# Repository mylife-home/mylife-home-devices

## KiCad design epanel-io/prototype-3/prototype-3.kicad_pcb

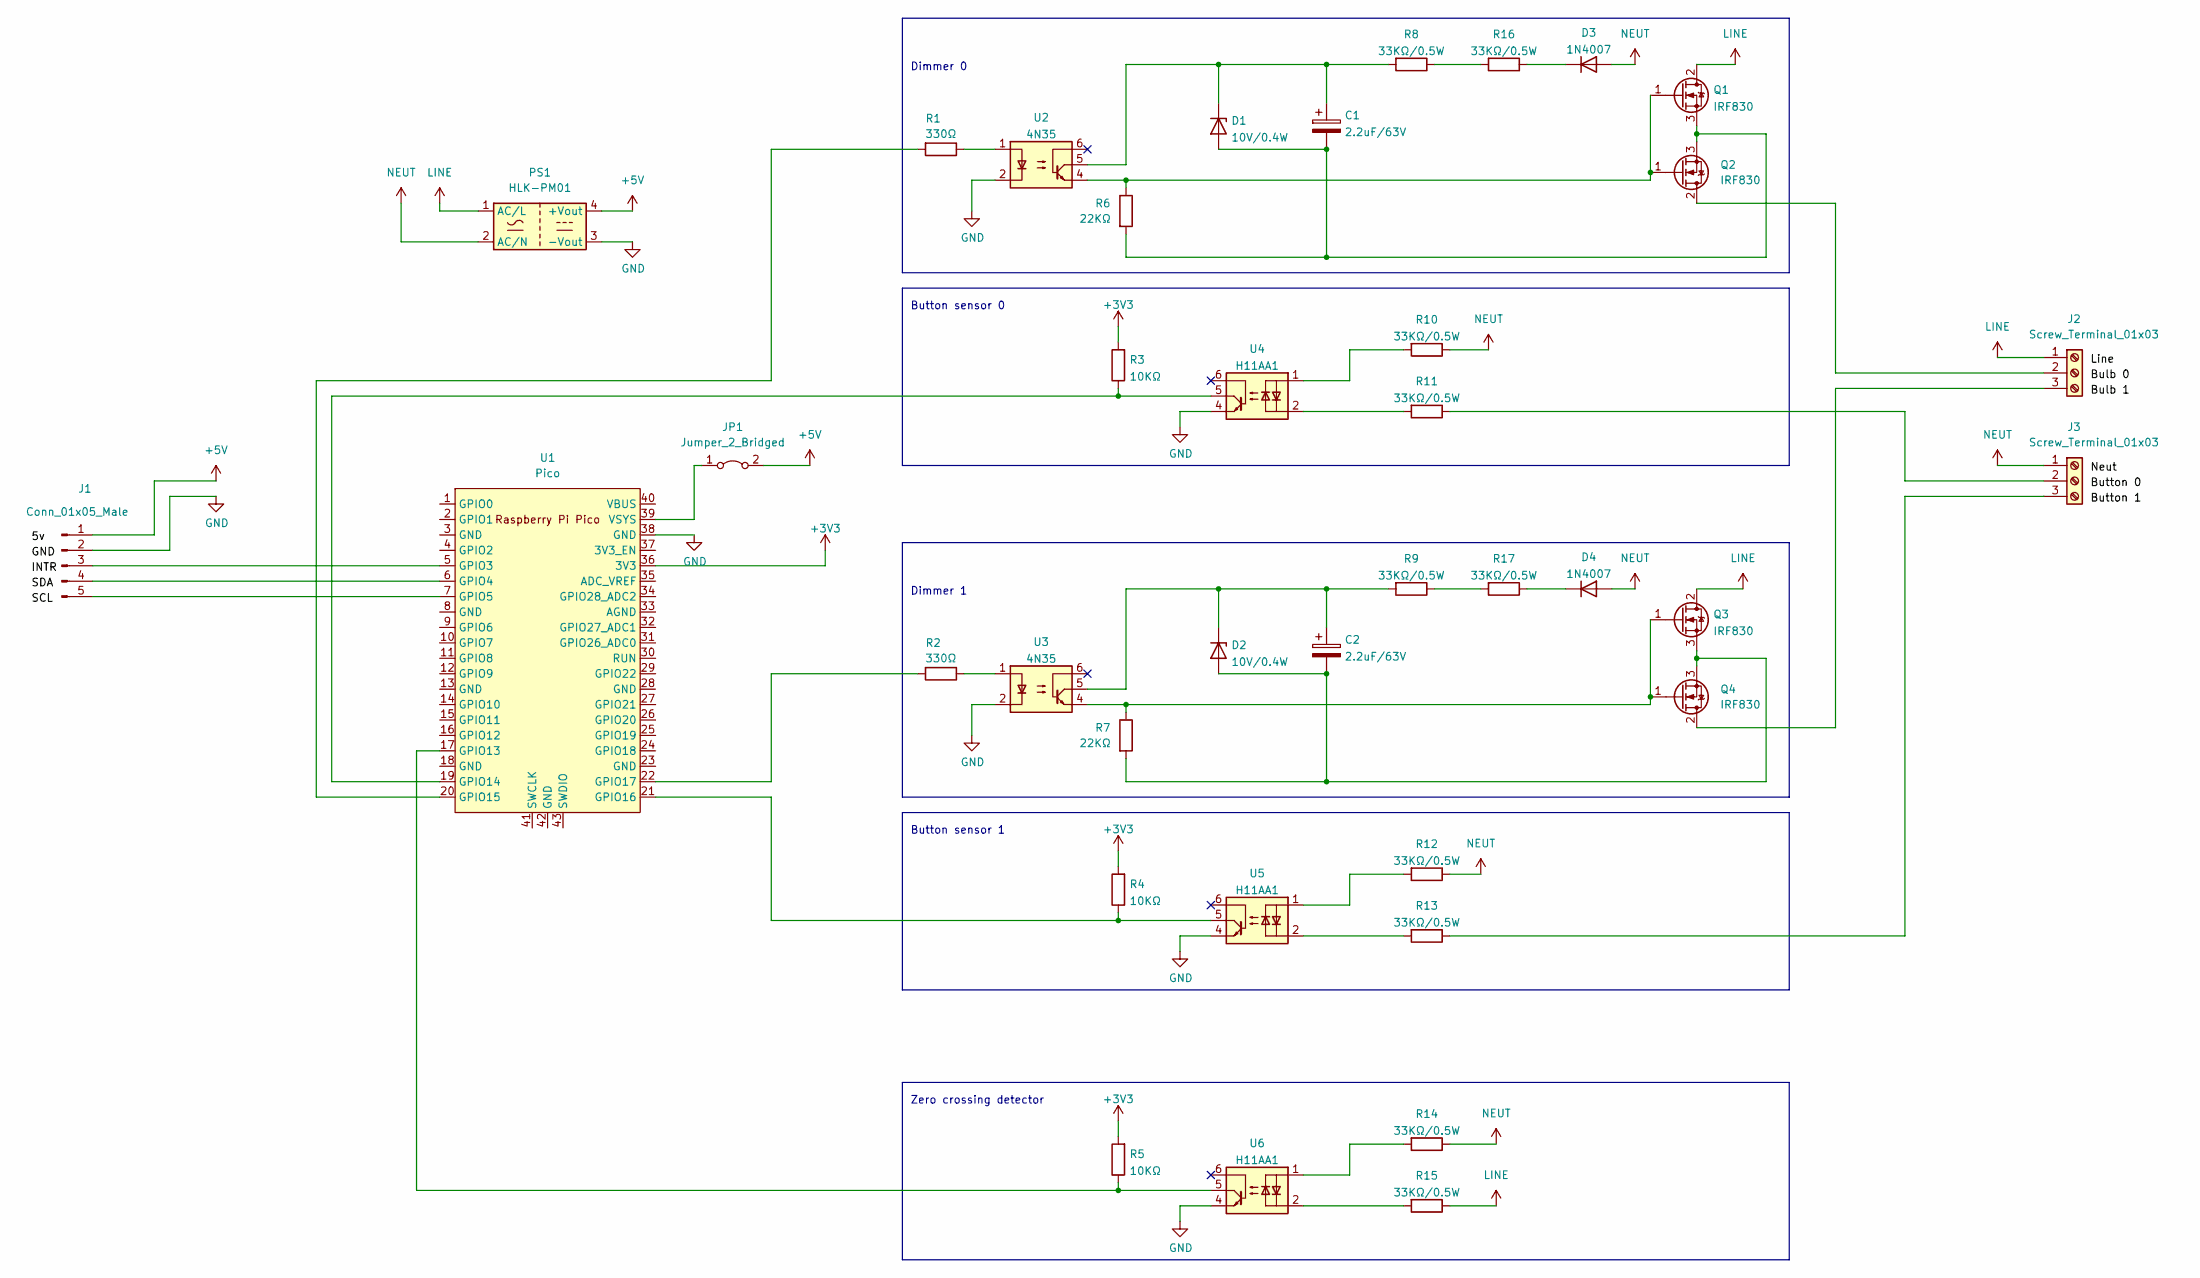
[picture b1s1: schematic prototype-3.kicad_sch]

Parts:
C1, C2: 2.2uF/63V; C_1206_3216Metric; LCSC C50254
D1, D2: 10V/0.4W; D_SOD-123; LCSC C173431
D3, D4: 1N4007; D_SMA; LCSC C727081
J1: Conn_01x05_Male; PinHeader_1x05_P2.54mm_Vertical
J2, J3: Screw_Terminal_01x03; TerminalBlock_bornier-3_P5.08mm
JP1: Jumper_2_Bridged; PinHeader_1x02_P2.54mm_Vertical
PS1: HLK-PM01; Converter_ACDC_HiLink_HLK-PMxx
Q1, Q2, Q3, Q4: IRF830; TO-263-3_TabPin2; LCSC C693297
R1, R2: 330Ω; R_0603_1608Metric; LCSC C23138
R3, R4, R5: 10KΩ; R_0603_1608Metric; LCSC C25804
R6, R7: 22KΩ; R_0603_1608Metric; LCSC C31850
R8, R9, R10, R11, R12, R13, R14, R15, R16, R17: 33KΩ/0.5W; R_0805_2012Metric; LCSC C966118
U1: Pico; RPi_Pico_SMD_TH
U2, U3: 4N35; SMDIP-6_W7.62mm; LCSC C115444
U4, U5, U6: H11AA1; SMDIP-6_W9.53mm; LCSC C184383

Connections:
+3V3: R3.2, R4.2, R5.2, U1.36 (3V3)
+5V: J1.1, JP1.2 (B), PS1.4 (+Vout)
GND: J1.2, PS1.3 (-Vout), U1.38 (GND), U2.2, U3.2, U4.4, U5.4, U6.4
LINE: J2.1, PS1.1 (AC/L), Q1.2 (D), Q3.2 (D), R15.1
NEUT: D3.2 (A), D4.2 (A), J3.1, PS1.2 (AC/N), R10.1, R12.1, R14.1
unnamed: C1.1, D1.1 (K), R8.2, U2.5
unnamed: C1.2, D1.2 (A), Q1.3 (S), Q2.3 (S), R6.2
unnamed: C2.1, D2.1 (K), R9.2, U3.5
unnamed: C2.2, D2.2 (A), Q3.3 (S), Q4.3 (S), R7.2
unnamed: D3.1 (K), R16.1
unnamed: D4.1 (K), R17.1
unnamed: J1.3, U1.5 (GPIO3)
unnamed: J1.4, U1.6 (GPIO4)
unnamed: J1.5, U1.7 (GPIO5)
unnamed: J2.2, Q2.2 (D)
unnamed: J2.3, Q4.2 (D)
unnamed: J3.2, R11.1
unnamed: J3.3, R13.1
unnamed: JP1.1 (A), U1.39 (VSYS)
unnamed: Q1.1 (G), Q2.1 (G), R6.1, U2.4
unnamed: Q3.1 (G), Q4.1 (G), R7.1, U3.4
unnamed: R1.1, U2.1
unnamed: R1.2, U1.20 (GPIO15)
unnamed: R2.1, U3.1
unnamed: R2.2, U1.22 (GPIO17)
unnamed: R3.1, U1.19 (GPIO14), U4.5
unnamed: R4.1, U1.21 (GPIO16), U5.5
unnamed: R5.1, U1.17 (GPIO13), U6.5
unnamed: R10.2, U4.1
unnamed: R11.2, U4.2
unnamed: R12.2, U5.1
unnamed: R13.2, U5.2
unnamed: R14.2, U6.1
unnamed: R15.2, U6.2
unnamed: R8.1, R16.2
unnamed: R9.1, R17.2

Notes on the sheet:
Button sensor 1
Button sensor 0
Dimmer 1
Dimmer 0
Zero crossing detector

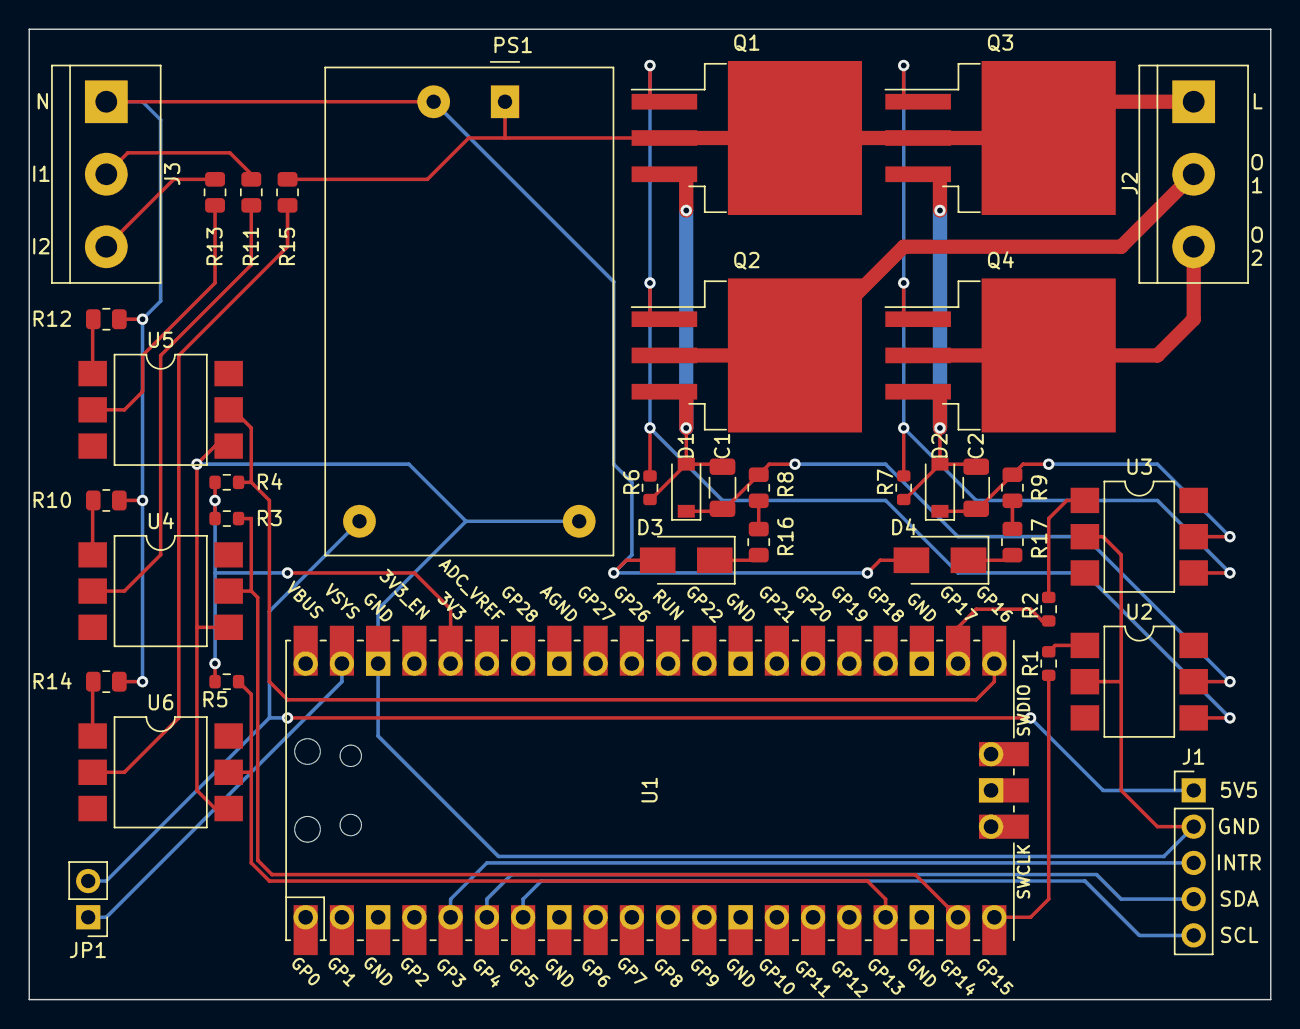
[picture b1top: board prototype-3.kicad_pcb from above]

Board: 2 copper layers, 87.0 x 68.0 mm, 38 parts (0 on the bottom side), 36 nets.

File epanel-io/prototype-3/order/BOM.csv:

Comment,Designator,Footprint,LCSC
"2.2uF/63V","C1,C2","Capacitor_SMD:C_1206_3216Metric","C50254"
"10V/0.4W","D1,D2","Diode_SMD:D_SOD-123","C173431"
"1N4007","D3,D4","Diode_SMD:D_SMA","C727081"
"Conn_01x05_Male","J1","Connector_PinHeader_2.54mm:PinHeader_1x05_P2.54mm_Vertical",""
"Screw_Terminal_01x03","J2,J3","TerminalBlock:TerminalBlock_bornier-3_P5.08mm",""
"Jumper_2_Bridged","JP1","Connector_PinHeader_2.54mm:PinHeader_1x02_P2.54mm_Vertical",""
"HLK-PM01","PS1","Converter_ACDC:Converter_ACDC_HiLink_HLK-PMxx",""
"IRF830","Q1,Q2,Q3,Q4","Package_TO_SOT_SMD:TO-263-3_TabPin2","C693297"
"330Ω","R1,R2","Resistor_SMD:R_0603_1608Metric","C23138"
"10KΩ","R3,R4,R5","Resistor_SMD:R_0603_1608Metric","C25804"
"22KΩ","R6,R7","Resistor_SMD:R_0603_1608Metric","C31850"
"33KΩ/0.5W","R8,R9,R10,R11,R12,R13,R14,R15,R16,R17","Resistor_SMD:R_0805_2012Metric","C966118"
"Pico","U1","MCU_RaspberryPi_and_Boards:RPi_Pico_SMD_TH",""
"4N35","U2,U3","Package_DIP:SMDIP-6_W7.62mm","C115444"
"H11AA1","U4,U5,U6","Package_DIP:SMDIP-6_W9.53mm","C184383"

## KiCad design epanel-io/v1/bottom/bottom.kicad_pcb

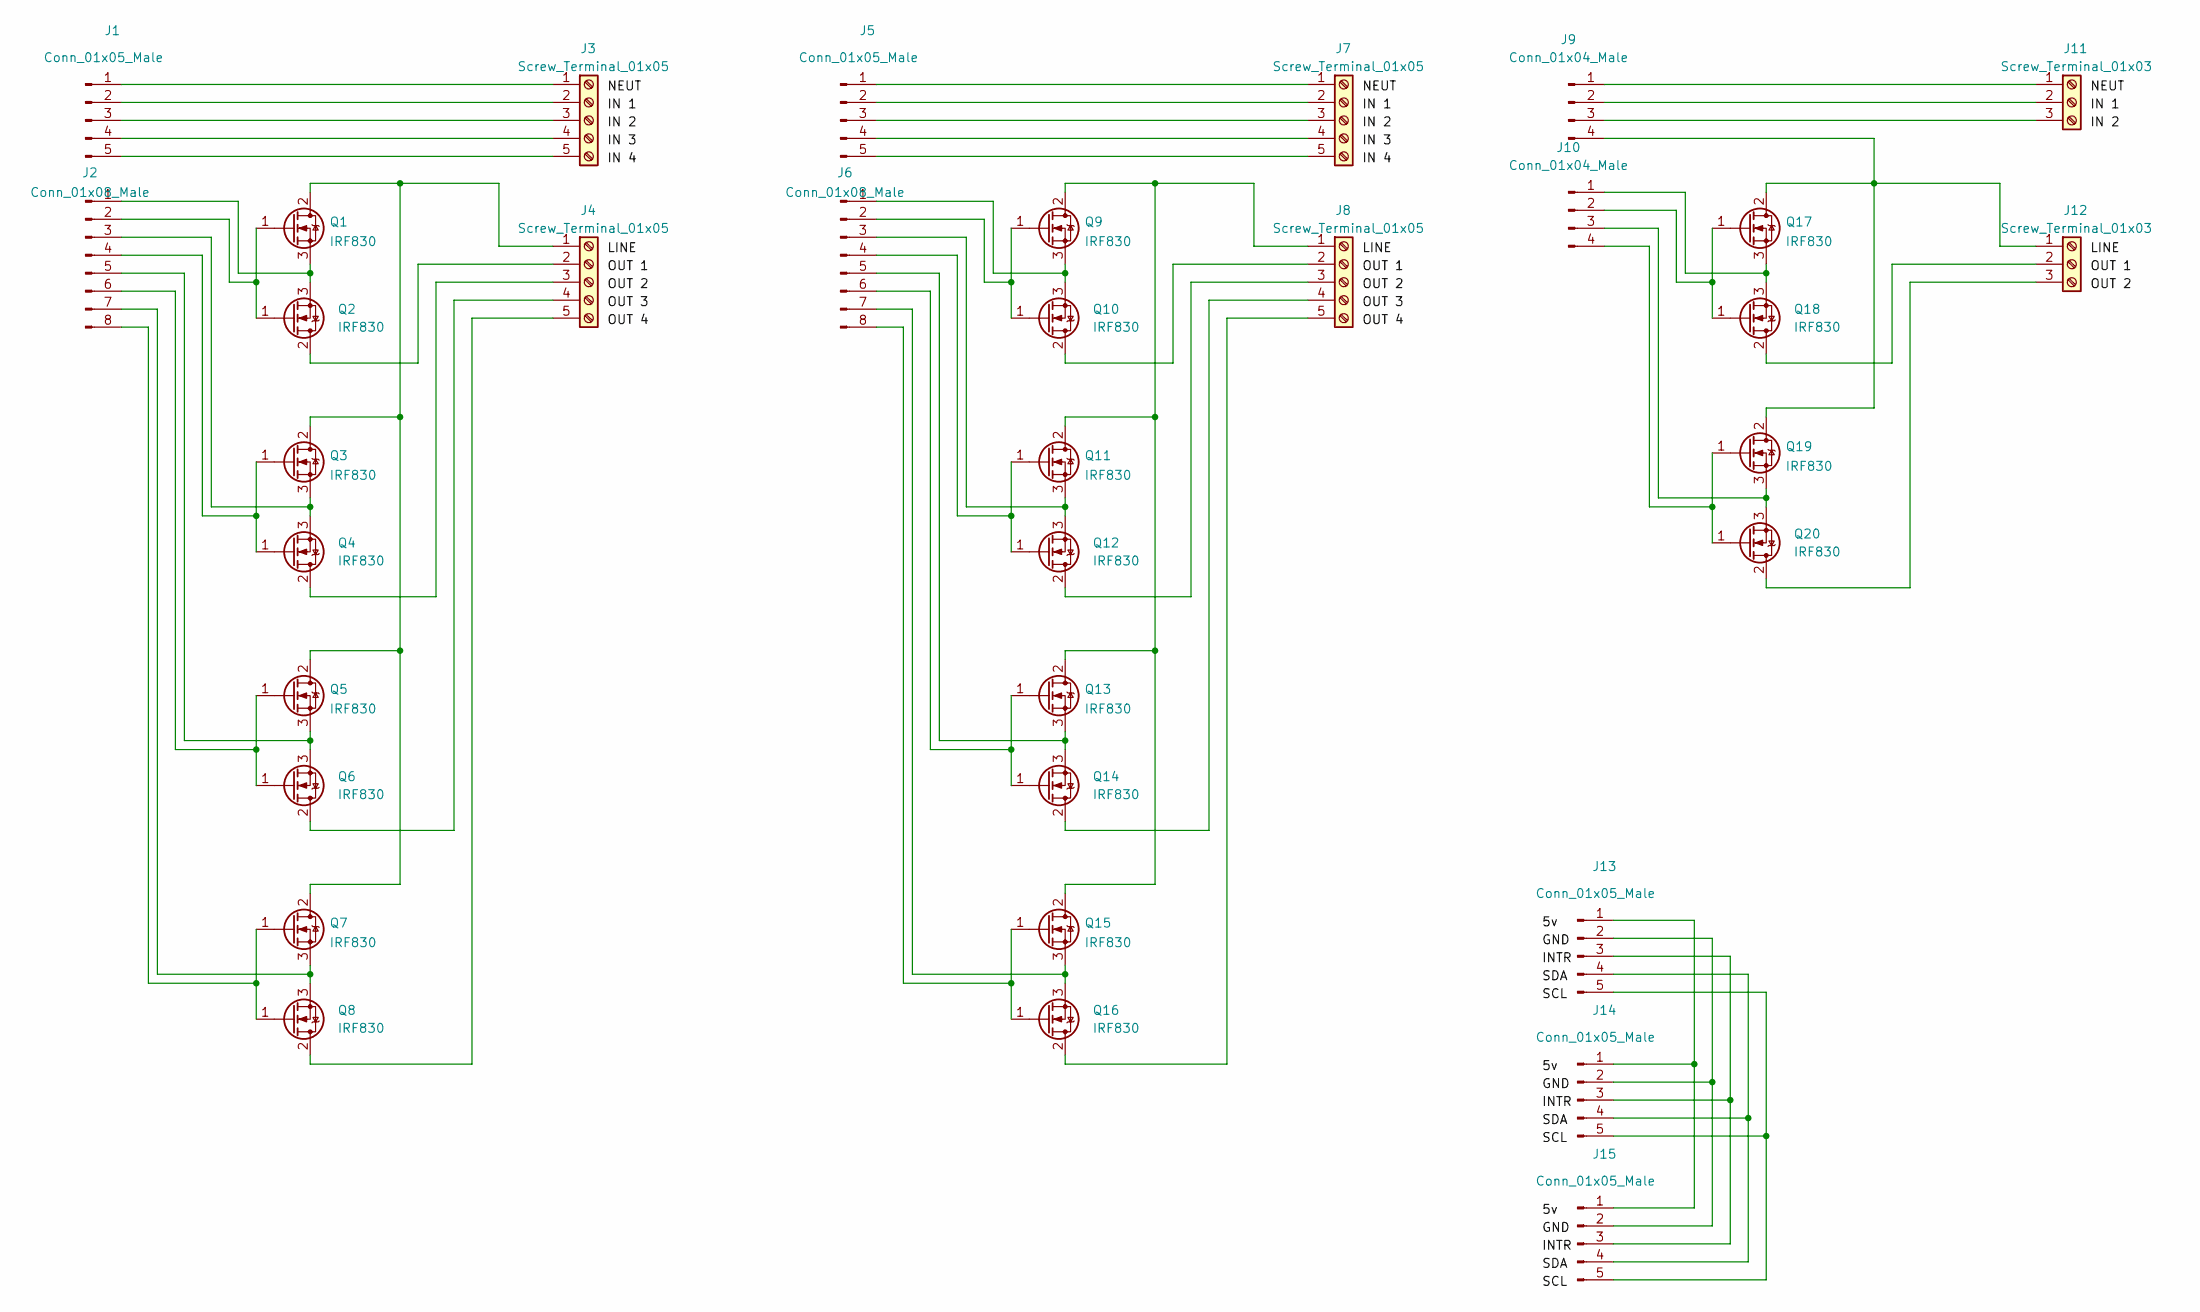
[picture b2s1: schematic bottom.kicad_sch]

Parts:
J1, J5, J13, J14, J15: Conn_01x05_Male; PinHeader_1x05_P2.54mm_Vertical
J2, J6: Conn_01x08_Male; PinHeader_1x08_P2.54mm_Vertical
J3, J4, J7, J8: Screw_Terminal_01x05; TerminalBlock_bornier-5_P5.08mm
J9, J10: Conn_01x04_Male; PinHeader_1x04_P2.54mm_Vertical
J11, J12: Screw_Terminal_01x03; TerminalBlock_bornier-3_P5.08mm
Q1, Q2, Q3, Q4, Q5, Q6, Q7, Q8, Q9, Q10, Q11, Q12, Q13, Q14, Q15, Q16, Q17, Q18, Q19, Q20: IRF830; TO-263-3_TabPin2; LCSC C693297

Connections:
unnamed: J1.1, J3.1
unnamed: J1.2, J3.2
unnamed: J1.3, J3.3
unnamed: J1.4, J3.4
unnamed: J1.5, J3.5
unnamed: J2.1, Q1.3 (S), Q2.3 (S)
unnamed: J2.2, Q1.1 (G), Q2.1 (G)
unnamed: J2.3, Q3.3 (S), Q4.3 (S)
unnamed: J2.4, Q3.1 (G), Q4.1 (G)
unnamed: J2.5, Q5.3 (S), Q6.3 (S)
unnamed: J2.6, Q5.1 (G), Q6.1 (G)
unnamed: J2.7, Q7.3 (S), Q8.3 (S)
unnamed: J2.8, Q7.1 (G), Q8.1 (G)
unnamed: J4.1, Q1.2 (D), Q3.2 (D), Q5.2 (D), Q7.2 (D)
unnamed: J4.2, Q2.2 (D)
unnamed: J4.3, Q4.2 (D)
unnamed: J4.4, Q6.2 (D)
unnamed: J4.5, Q8.2 (D)
unnamed: J5.1, J7.1
unnamed: J5.2, J7.2
unnamed: J5.3, J7.3
unnamed: J5.4, J7.4
unnamed: J5.5, J7.5
unnamed: J6.1, Q9.3 (S), Q10.3 (S)
unnamed: J6.2, Q9.1 (G), Q10.1 (G)
unnamed: J6.3, Q11.3 (S), Q12.3 (S)
unnamed: J6.4, Q11.1 (G), Q12.1 (G)
unnamed: J6.5, Q13.3 (S), Q14.3 (S)
unnamed: J6.6, Q13.1 (G), Q14.1 (G)
unnamed: J6.7, Q15.3 (S), Q16.3 (S)
unnamed: J6.8, Q15.1 (G), Q16.1 (G)
unnamed: J8.1, Q9.2 (D), Q11.2 (D), Q13.2 (D), Q15.2 (D)
unnamed: J8.2, Q10.2 (D)
unnamed: J8.3, Q12.2 (D)
unnamed: J8.4, Q14.2 (D)
unnamed: J8.5, Q16.2 (D)
unnamed: J10.1, Q17.3 (S), Q18.3 (S)
unnamed: J10.2, Q17.1 (G), Q18.1 (G)
unnamed: J10.3, Q19.3 (S), Q20.3 (S)
unnamed: J10.4, Q19.1 (G), Q20.1 (G)
unnamed: J9.1, J11.1
unnamed: J9.2, J11.2
unnamed: J9.3, J11.3
unnamed: J9.4, J12.1, Q17.2 (D), Q19.2 (D)
unnamed: J12.2, Q18.2 (D)
unnamed: J12.3, Q20.2 (D)
unnamed: J13.1, J14.1, J15.1
unnamed: J13.2, J14.2, J15.2
unnamed: J13.3, J14.3, J15.3
unnamed: J13.4, J14.4, J15.4
unnamed: J13.5, J14.5, J15.5

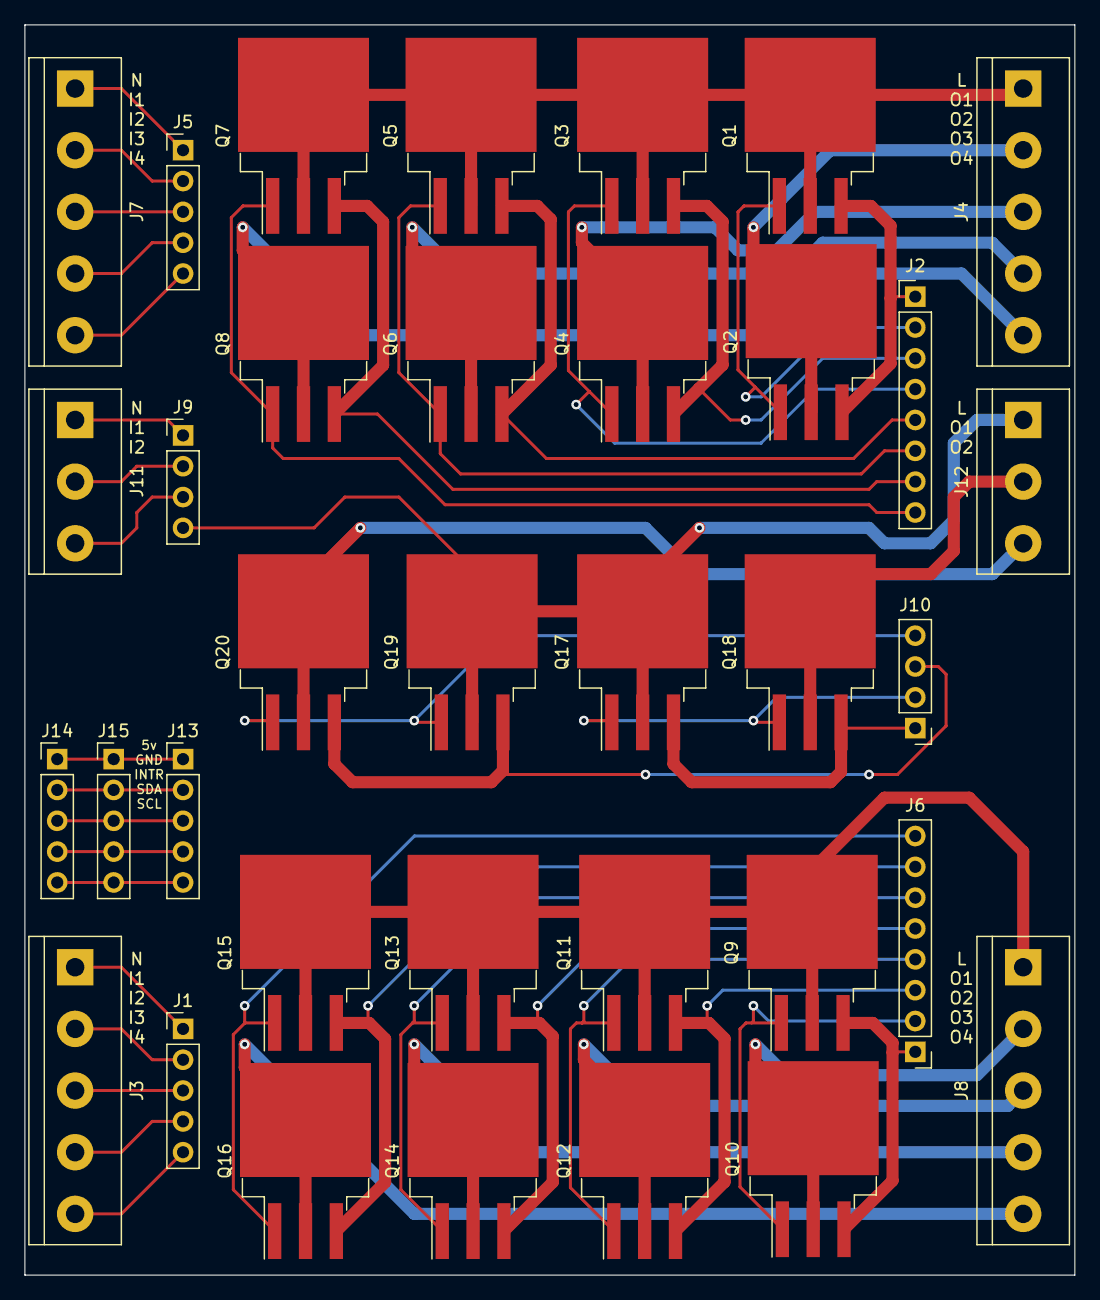
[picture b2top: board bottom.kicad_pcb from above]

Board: 2 copper layers, 86.5 x 103.0 mm, 35 parts (0 on the bottom side), 51 nets.

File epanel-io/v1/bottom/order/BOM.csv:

Comment,Designator,Footprint,LCSC
"Conn_01x05_Male","J1,J5,J13,J14,J15","Connector_PinHeader_2.54mm:PinHeader_1x05_P2.54mm_Vertical",""
"Screw_Terminal_01x03","J11,J12","TerminalBlock:TerminalBlock_bornier-3_P5.08mm",""
"Conn_01x08_Male","J2,J6","Connector_PinHeader_2.54mm:PinHeader_1x08_P2.54mm_Vertical",""
"Screw_Terminal_01x05","J3,J4,J7,J8","TerminalBlock:TerminalBlock_bornier-5_P5.08mm",""
"Conn_01x04_Male","J9,J10","Connector_PinHeader_2.54mm:PinHeader_1x04_P2.54mm_Vertical",""
"IRF830","Q1,Q2,Q3,Q4,Q5,Q6,Q7,Q8,Q9,Q10,Q11,Q12,Q13,Q14,Q15,Q16,Q17,Q18,Q19,Q20","Package_TO_SOT_SMD:TO-263-3_TabPin2","C693297"

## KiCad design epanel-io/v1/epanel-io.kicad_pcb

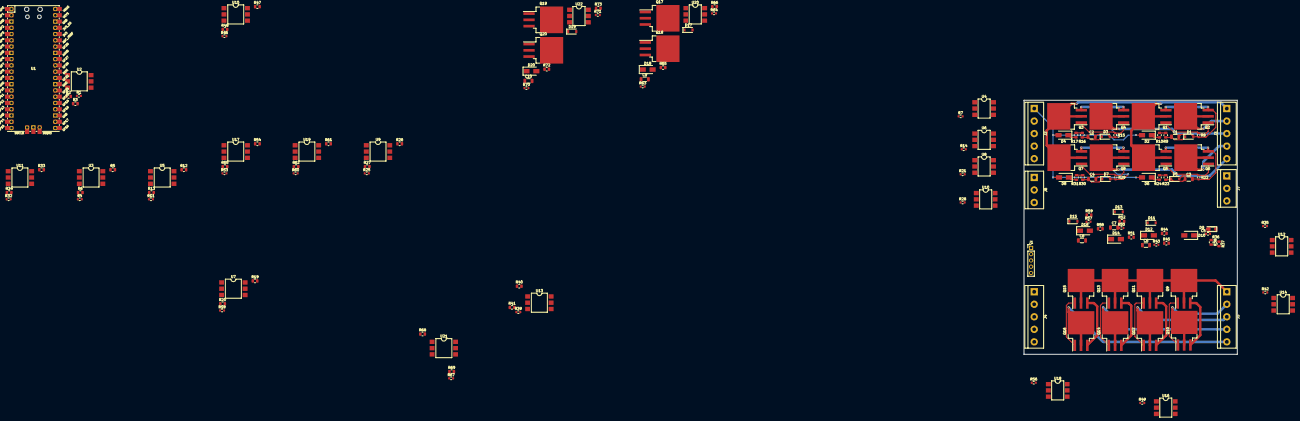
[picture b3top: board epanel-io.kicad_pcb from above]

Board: 2 copper layers, 86.5 x 103.0 mm, 152 parts (0 on the bottom side), 135 nets.

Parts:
C1, C2, C3, C4, C5, C6, C7, C8, C9, C10: 2.2uF/63V; C_1206_3216Metric
D1, D3, D5, D7, D9, D11, D13, D15, D17, D19: 10V/0.4W; D_SOD-123
D2, D4, D6, D8, D10, D12, D14, D16, D18, D20: 1N4007; D_SMA
J1: Conn_01x05_Male; PinHeader_1x05_P2.54mm_Vertical
J2, J3, J4, J5: Screw_Terminal_01x05; TerminalBlock_bornier-5_P5.08mm
J6, J7: Screw_Terminal_01x03; TerminalBlock_bornier-3_P5.08mm
Q1, Q2, Q3, Q4, Q5, Q6, Q7, Q8, Q9, Q10, Q11, Q12, Q13, Q14, Q15, Q16, Q17, Q18, Q19, Q20: IRF830; TO-263-3_TabPin2
R1, R4, R11, R18, R25, R32, R39, R46, R53, R60, R67: 10KΩ; R_0603_1608Metric
R2, R3, R5, R6, R9, R10, R12, R13, R16, R17, R19, R20, R23, R24, R26, R27, R30, R31, R33, R34, R37, R38, R40, R41, R44, R45, R47, R48, R51, R52, R54, R55, R58, R59, R61, R62, R65, R66, R68, R69, R72, R73: 33KΩ/0.5W; R_0805_2012Metric
R7, R14, R21, R28, R35, R42, R49, R56, R63, R70: 330Ω; R_0603_1608Metric
R8, R15, R22, R29, R36, R43, R50, R57, R64, R71: 22KΩ; R_0603_1608Metric
U1: Pico; RPi_Pico_SMD_TH
U2, U3, U5, U7, U9, U11, U13, U15, U17, U19, U21: H11AA1; SMDIP-6_W9.53mm
U4, U6, U8, U10, U12, U14, U16, U18, U20, U22: 4N35; SMDIP-6_W7.62mm

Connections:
+3V3: R1.2, R4.2, R11.2, R18.2, R25.2, R32.2, R39.2, R46.2, R53.2, R60.2, R67.2, U1.36 (3V3)
+5V: J1.1, U1.39 (VSYS)
/Input 1/INPUT: J2.2, R6.1
/Input 1/NEUT: D2.2 (A), D4.2 (A), D6.2 (A), D8.2 (A), J2.1, R5.1, R12.1, R19.1, R26.1
/Input 1/RPI: R4.1, U1.9 (GPIO6), U3.5
/Input 2/INPUT: J2.3, R13.1
/Input 2/RPI: R11.1, U1.10 (GPIO7), U5.5
/Input 3/INPUT: J2.4, R20.1
/Input 3/RPI: R18.1, U1.11 (GPIO8), U7.5
/Input 4/INPUT: J2.5, R27.1
/Input 4/RPI: R25.1, U1.12 (GPIO9), U9.5
/Input 5/INPUT: J4.2, R34.1
/Input 5/NEUT: D10.2 (A), D12.2 (A), D14.2 (A), D16.2 (A), J4.1, R33.1, R40.1, R47.1, R54.1
/Input 5/RPI: R32.1, U1.19 (GPIO14), U11.5
/Input 6/INPUT: J4.3, R41.1
/Input 6/RPI: R39.1, U1.20 (GPIO15), U13.5
/Input 7/INPUT: J4.4, R48.1
/Input 7/RPI: R46.1, U1.21 (GPIO16), U15.5
/Input 8/INPUT: J4.5, R55.1
/Input 8/RPI: R53.1, U1.22 (GPIO17), U17.5
/Input 9/INPUT: J6.2, R62.1
/Input 9/RPI: R60.1, U1.29 (GPIO22), U19.5
/Input 10/INPUT: J6.3, R69.1
/Input 10/NEUT: D18.2 (A), D20.2 (A), J6.1, R2.1, R61.1, R68.1
/Input 10/RPI: R67.1, U1.31 (GPIO26_ADC0), U21.5
/Output 1/LINE: J3.1, Q1.2 (D), Q3.2 (D), Q5.2 (D), Q7.2 (D)
/Output 1/OUTPUT: J3.2, Q2.2 (D)
/Output 1/RPI: R7.2, U1.14 (GPIO10)
/Output 2/OUTPUT: J3.3, Q4.2 (D)
/Output 2/RPI: R14.2, U1.15 (GPIO11)
/Output 3/OUTPUT: J3.4, Q6.2 (D)
/Output 3/RPI: R21.2, U1.16 (GPIO12)
/Output 4/OUTPUT: J3.5, Q8.2 (D)
/Output 4/RPI: R28.2, U1.17 (GPIO13)
/Output 5/LINE: J5.1, Q9.2 (D), Q11.2 (D), Q13.2 (D), Q15.2 (D)
/Output 5/OUTPUT: J5.2, Q10.2 (D)
/Output 5/RPI: R35.2, U1.24 (GPIO18)
/Output 6/OUTPUT: J5.4, Q14.2 (D)
/Output 6/RPI: R49.2, U1.26 (GPIO20)
/Output 7/OUTPUT: J5.3, Q12.2 (D)
/Output 7/RPI: R42.2, U1.25 (GPIO19)
/Output 8/OUTPUT: J5.5, Q16.2 (D)
/Output 8/RPI: R56.2, U1.27 (GPIO21)
/Output 9/OUTPUT: J7.2, Q18.2 (D)
/Output 9/RPI: R63.2, U1.32 (GPIO27_ADC1)
/Output 10/LINE: J7.1, Q17.2 (D), Q19.2 (D), R3.1
/Output 10/OUTPUT: J7.3, Q20.2 (D)
/Output 10/RPI: R70.2, U1.34 (GPIO28_ADC2)
GND: J1.2, U1.38 (GND), U2.4, U3.4, U4.2, U5.4, U6.2, U7.4, U8.2, U9.4, U10.2, U11.4, U12.2, U13.4, U14.2, U15.4, U16.2, U17.4, U18.2, U19.4, U20.2, U21.4, U22.2
unnamed: C1.1, D1.1 (K), R9.2, U4.5
unnamed: C1.2, D1.2 (A), Q1.3 (S), Q2.3 (S), R8.2
unnamed: C2.1, D3.1 (K), R16.2, U6.5
unnamed: C2.2, D3.2 (A), Q3.3 (S), Q4.3 (S), R15.2
unnamed: C3.1, D5.1 (K), R23.2, U8.5
unnamed: C3.2, D5.2 (A), Q5.3 (S), Q6.3 (S), R22.2
unnamed: C4.1, D7.1 (K), R30.2, U10.5
unnamed: C4.2, D7.2 (A), Q7.3 (S), Q8.3 (S), R29.2
unnamed: C5.1, D9.1 (K), R37.2, U12.5
unnamed: C5.2, D9.2 (A), Q9.3 (S), Q10.3 (S), R36.2
unnamed: C6.1, D11.1 (K), R44.2, U14.5
unnamed: C6.2, D11.2 (A), Q11.3 (S), Q12.3 (S), R43.2
unnamed: C7.1, D13.1 (K), R51.2, U16.5
unnamed: C7.2, D13.2 (A), Q13.3 (S), Q14.3 (S), R50.2
unnamed: C8.1, D15.1 (K), R58.2, U18.5
unnamed: C8.2, D15.2 (A), Q15.3 (S), Q16.3 (S), R57.2
unnamed: C9.1, D17.1 (K), R65.2, U20.5
unnamed: C9.2, D17.2 (A), Q17.3 (S), Q18.3 (S), R64.2
unnamed: C10.1, D19.1 (K), R72.2, U22.5
unnamed: C10.2, D19.2 (A), Q19.3 (S), Q20.3 (S), R71.2
unnamed: D2.1 (K), R10.1
unnamed: D4.1 (K), R17.1
unnamed: D6.1 (K), R24.1
unnamed: D8.1 (K), R31.1
unnamed: D10.1 (K), R38.1
unnamed: D12.1 (K), R45.1
unnamed: D14.1 (K), R52.1
unnamed: D16.1 (K), R59.1
unnamed: D18.1 (K), R66.1
unnamed: D20.1 (K), R73.1
unnamed: J1.3, U1.5 (GPIO3)
unnamed: J1.4, U1.6 (GPIO4)
unnamed: J1.5, U1.7 (GPIO5)
unnamed: Q1.1 (G), Q2.1 (G), R8.1, U4.4
unnamed: Q3.1 (G), Q4.1 (G), R15.1, U6.4
unnamed: Q5.1 (G), Q6.1 (G), R22.1, U8.4
unnamed: Q7.1 (G), Q8.1 (G), R29.1, U10.4
unnamed: Q9.1 (G), Q10.1 (G), R36.1, U12.4
unnamed: Q11.1 (G), Q12.1 (G), R43.1, U14.4
unnamed: Q13.1 (G), Q14.1 (G), R50.1, U16.4
unnamed: Q15.1 (G), Q16.1 (G), R57.1, U18.4
unnamed: Q17.1 (G), Q18.1 (G), R64.1, U20.4
unnamed: Q19.1 (G), Q20.1 (G), R71.1, U22.4
unnamed: R1.1, U1.4 (GPIO2), U2.5
unnamed: R2.2, U2.1
unnamed: R3.2, U2.2
unnamed: R5.2, U3.1
unnamed: R6.2, U3.2
unnamed: R7.1, U4.1
unnamed: R9.1, R10.2
unnamed: R12.2, U5.1
unnamed: R13.2, U5.2
unnamed: R14.1, U6.1
unnamed: R16.1, R17.2
unnamed: R19.2, U7.1
unnamed: R20.2, U7.2
unnamed: R21.1, U8.1
unnamed: R23.1, R24.2
unnamed: R26.2, U9.1
unnamed: R27.2, U9.2
unnamed: R28.1, U10.1
unnamed: R30.1, R31.2
unnamed: R33.2, U11.1
unnamed: R34.2, U11.2
unnamed: R35.1, U12.1
unnamed: R37.1, R38.2
unnamed: R40.2, U13.1
unnamed: R41.2, U13.2
unnamed: R42.1, U14.1
unnamed: R44.1, R45.2
unnamed: R47.2, U15.1
unnamed: R48.2, U15.2
unnamed: R49.1, U16.1
unnamed: R51.1, R52.2
unnamed: R54.2, U17.1
unnamed: R55.2, U17.2
unnamed: R56.1, U18.1
unnamed: R58.1, R59.2
unnamed: R61.2, U19.1
unnamed: R62.2, U19.2
unnamed: R63.1, U20.1
unnamed: R65.1, R66.2
unnamed: R68.2, U21.1
unnamed: R69.2, U21.2
unnamed: R70.1, U22.1
unnamed: R72.1, R73.2

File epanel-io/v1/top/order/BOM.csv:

Comment,Designator,Footprint,LCSC
"2.2uF/63V","C1,C2,C3,C4,C5,C6,C7,C8,C9,C10","Capacitor_SMD:C_1206_3216Metric","C50254"
"10V/0.4W","D1,D3,D5,D7,D9,D11,D13,D15,D17,D19","Diode_SMD:D_SOD-123","C173431"
"1N4007","D2,D4,D6,D8,D10,D12,D14,D16,D18,D20","Diode_SMD:D_SMA","C727081"
"Conn_01x05_Male","J1","Connector_PinHeader_2.54mm:PinHeader_1x05_P2.54mm_Vertical",""
"Conn_01x05_Female","J2,J4","Connector_PinHeader_2.54mm:PinHeader_1x05_P2.54mm_Vertical",""
"Conn_01x08_Female","J3,J5","Connector_PinHeader_2.54mm:PinHeader_1x08_P2.54mm_Vertical",""
"Conn_01x04_Female","J6,J7","Connector_PinHeader_2.54mm:PinHeader_1x04_P2.54mm_Vertical",""
"10KΩ","R1,R4,R11,R18,R25,R32,R39,R46,R53,R60,R67","Resistor_SMD:R_0603_1608Metric","C25804"
"33KΩ/0.5W","R2,R3,R5,R6,R9,R10,R12,R13,R16,R17,R19,R20,R23,R24,R26,R27,R30,R31,R33,R34,R37,R38,R40,R41,R44,R45,R47,R48,R51,R52,R54,R55,R58,R59,R61,R62,R65,R66,R68,R69,R72,R73","Resistor_SMD:R_0805_2012Metric","C966118"
"330Ω","R7,R14,R21,R28,R35,R42,R49,R56,R63,R70","Resistor_SMD:R_0603_1608Metric","C23138"
"22KΩ","R8,R15,R22,R29,R36,R43,R50,R57,R64,R71","Resistor_SMD:R_0603_1608Metric","C31850"
"Pico","U1","Custom:RPI_Pico_pinout",""
"H11AA1","U2,U3,U5,U7,U9,U11,U13,U15,U17,U19,U21","Package_DIP:SMDIP-6_W9.53mm","C184383"
"4N35","U4,U6,U8,U10,U12,U14,U16,U18,U20,U22","Package_DIP:SMDIP-6_W7.62mm","C115444"

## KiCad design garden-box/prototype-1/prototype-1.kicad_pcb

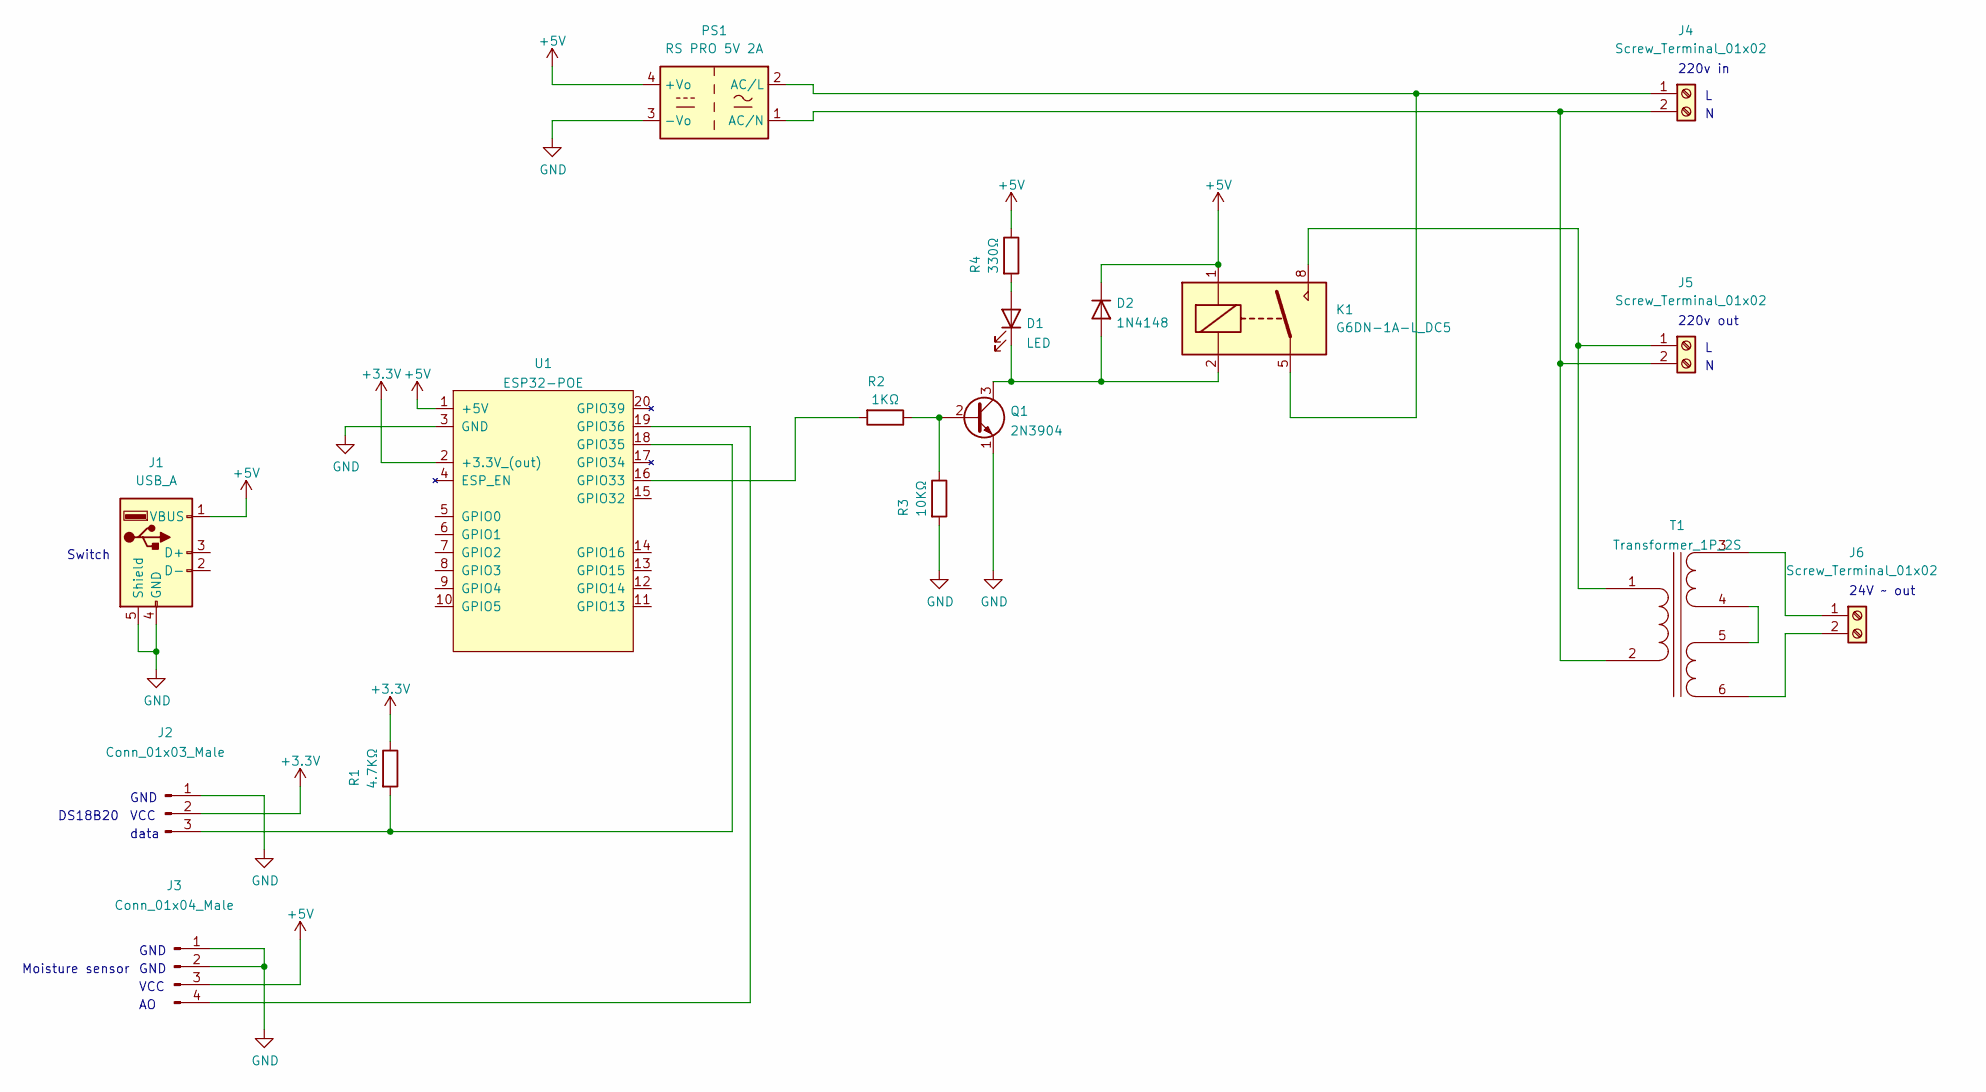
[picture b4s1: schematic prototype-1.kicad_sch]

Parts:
D1: LED; D_0805_2012Metric; LCSC C2297
D2: 1N4148; D_SOD-123; LCSC C81598
J1: USB_A; USB_A_Molex_67643_Horizontal
J2: Conn_01x03_Male; PinHeader_1x03_P2.54mm_Vertical
J3: Conn_01x04_Male; PinHeader_1x04_P2.54mm_Vertical
J4, J5, J6: Screw_Terminal_01x02; TerminalBlock_bornier-2_P5.08mm
K1: G6DN-1A-L_DC5; G6DN-1A-L
PS1: RS PRO 5V 2A
Q1: 2N3904; SOT-23; LCSC C18536
R1: 4.7KΩ; R_0402_1005Metric; LCSC C25900
R2: 1KΩ; R_0402_1005Metric; LCSC C11702
R3: 10KΩ; R_0402_1005Metric; LCSC C25744
R4: 330Ω; R_0402_1005Metric; LCSC C25104
T1: Transformer_1P_2S; VCM36212
U1: ESP32-POE

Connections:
+3V3: J2.2, R1.1, U1.2 (+3.3V_(out))
+5V: D2.1 (K), J1.1 (VBUS), J3.3, K1.1, PS1.4 (+Vo), R4.1, U1.1 (+5V)
GND: J1.4 (GND), J1.5 (Shield), J2.1, J3.1, J3.2, PS1.3 (-Vo), Q1.1 (E), R3.2, U1.3 (GND)
unnamed: D1.1 (K), D2.2 (A), K1.2, Q1.3 (C)
unnamed: D1.2 (A), R4.2
unnamed: J2.3, R1.2, U1.18 (GPIO35)
unnamed: J3.4, U1.19 (GPIO36)
unnamed: J4.1, K1.5, PS1.2 (AC/L)
unnamed: J4.2, J5.2, PS1.1 (AC/N), T1.2 (AB)
unnamed: J5.1, K1.8, T1.1 (AA)
unnamed: J6.1, T1.3 (SA)
unnamed: J6.2, T1.6 (SD)
unnamed: Q1.2 (B), R2.1, R3.1
unnamed: R2.2, U1.16 (GPIO33)
unnamed: T1.4 (SB), T1.5 (SC)

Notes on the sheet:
Moisture sensor
DS18B20
220v out
data
VCC
Switch
GND
220v in
24V ~ out

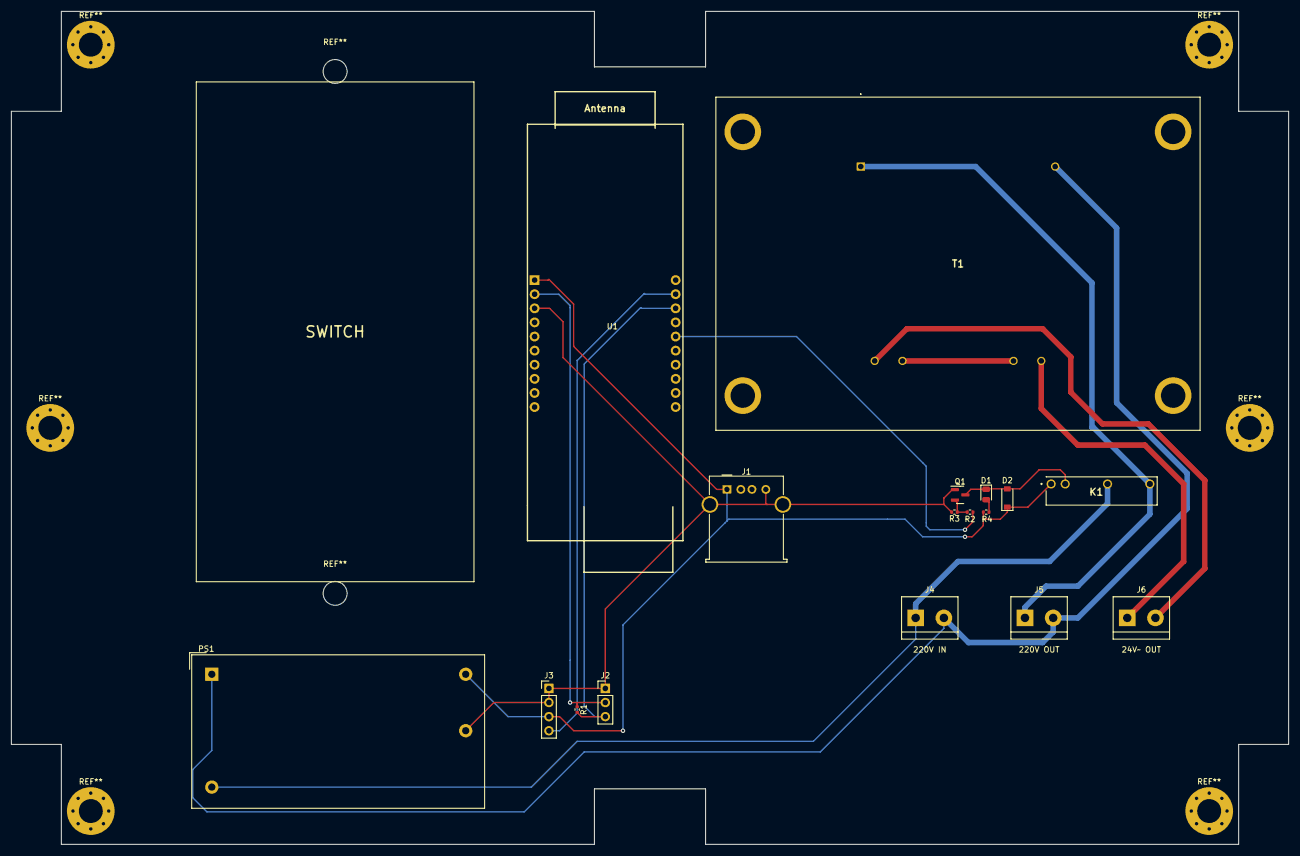
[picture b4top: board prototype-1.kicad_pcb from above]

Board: 2 copper layers, 230.0 x 150.0 mm, 17 parts (0 on the bottom side), 15 nets.

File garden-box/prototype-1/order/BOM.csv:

Comment,Designator,Footprint,LCSC
"LED","D1","Diode_SMD:D_0805_2012Metric","C2297"
"1N4148","D2","Diode_SMD:D_SOD-123","C81598"
"USB_A","J1","Connector_USB:USB_A_Molex_67643_Horizontal",""
"Conn_01x03_Male","J2","Connector_PinHeader_2.54mm:PinHeader_1x03_P2.54mm_Vertical",""
"Conn_01x04_Male","J3","Connector_PinHeader_2.54mm:PinHeader_1x04_P2.54mm_Vertical",""
"Screw_Terminal_01x02","J4,J5,J6","TerminalBlock:TerminalBlock_bornier-2_P5.08mm",""
"G6DN-1A-L_DC5","K1","rs-online:G6DN-1A-L",""
"RS PRO 5V 2A","PS1","mylife-footprints:RS PRO 5V 2A",""
"2N3904","Q1","Package_TO_SOT_SMD:SOT-23","C18536"
"4.7KΩ","R1","Resistor_SMD:R_0402_1005Metric","C25900"
"1KΩ","R2","Resistor_SMD:R_0402_1005Metric","C11702"
"10KΩ","R3","Resistor_SMD:R_0402_1005Metric","C25744"
"330Ω","R4","Resistor_SMD:R_0402_1005Metric","C25104"
"Transformer_1P_2S","T1","rs-online:VCM36212",""
"ESP32-POE","U1","mylife-footprints:ESP32-POE",""
